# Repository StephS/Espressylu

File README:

This is a preliminary design for a 32bit control board, based on the Atmel SAM3A Microcontroller.
A few features:
4 Layer construction
Designed for 24v Operation
Native MicroSD
Polulu style stepper motor controllers

This board is designed for 24v operation only. A 20v OVLO is enabled on the main voltage regulator to prevent 12v operation. Because of this I removed any 12v power supply connectors.
The Hotbed, Hotend, Fan and Z Probe all have 24v connections. The Z Endstop uses a 4 pin configuration instead of a 3 pin. The extra pin supplies 24v for use with additional probes. Please be sure your probe can use 24v, or use an adapter with a 12v regulator to supply the normal 12v for the probe.

Since this version (version 0.6) is preliminary, I do not recommend its use until the design can be verified.
A BOM and PIN Mapping will be developed and shared as the design matures.

If you'd like to donate so I can buy the full version of Eagle, and make more cool stuff, please contact me through Google+ at https://plus.google.com/+StephanieS3D

Disclaimer:
These designs are provided without any warrenty, expressed or implied. This is a prototype designed for hobbiest use only.
Care should be taken during use and appropriate safety precautions taken.
The author is providing this item "as is". The author does not provide any warranty of the item whatsoever, whether express, implied, or statutory, including, but not limited to, any warranty of merchantability or fitness for a particular purpose or any warranty that the contents of the item will be error-free.
In no respect shall the author incur any liability for any damages, including, but limited to, direct, indirect, special, or consequential damages arising out of, resulting from, or any way connected to the use of the item, whether or not based upon warranty, contract, tort, or otherwise; whether or not injury was sustained by persons or property or otherwise; and whether or not loss was sustained from, or arose out of, the results of, the item, or any services that may be provided by the author.

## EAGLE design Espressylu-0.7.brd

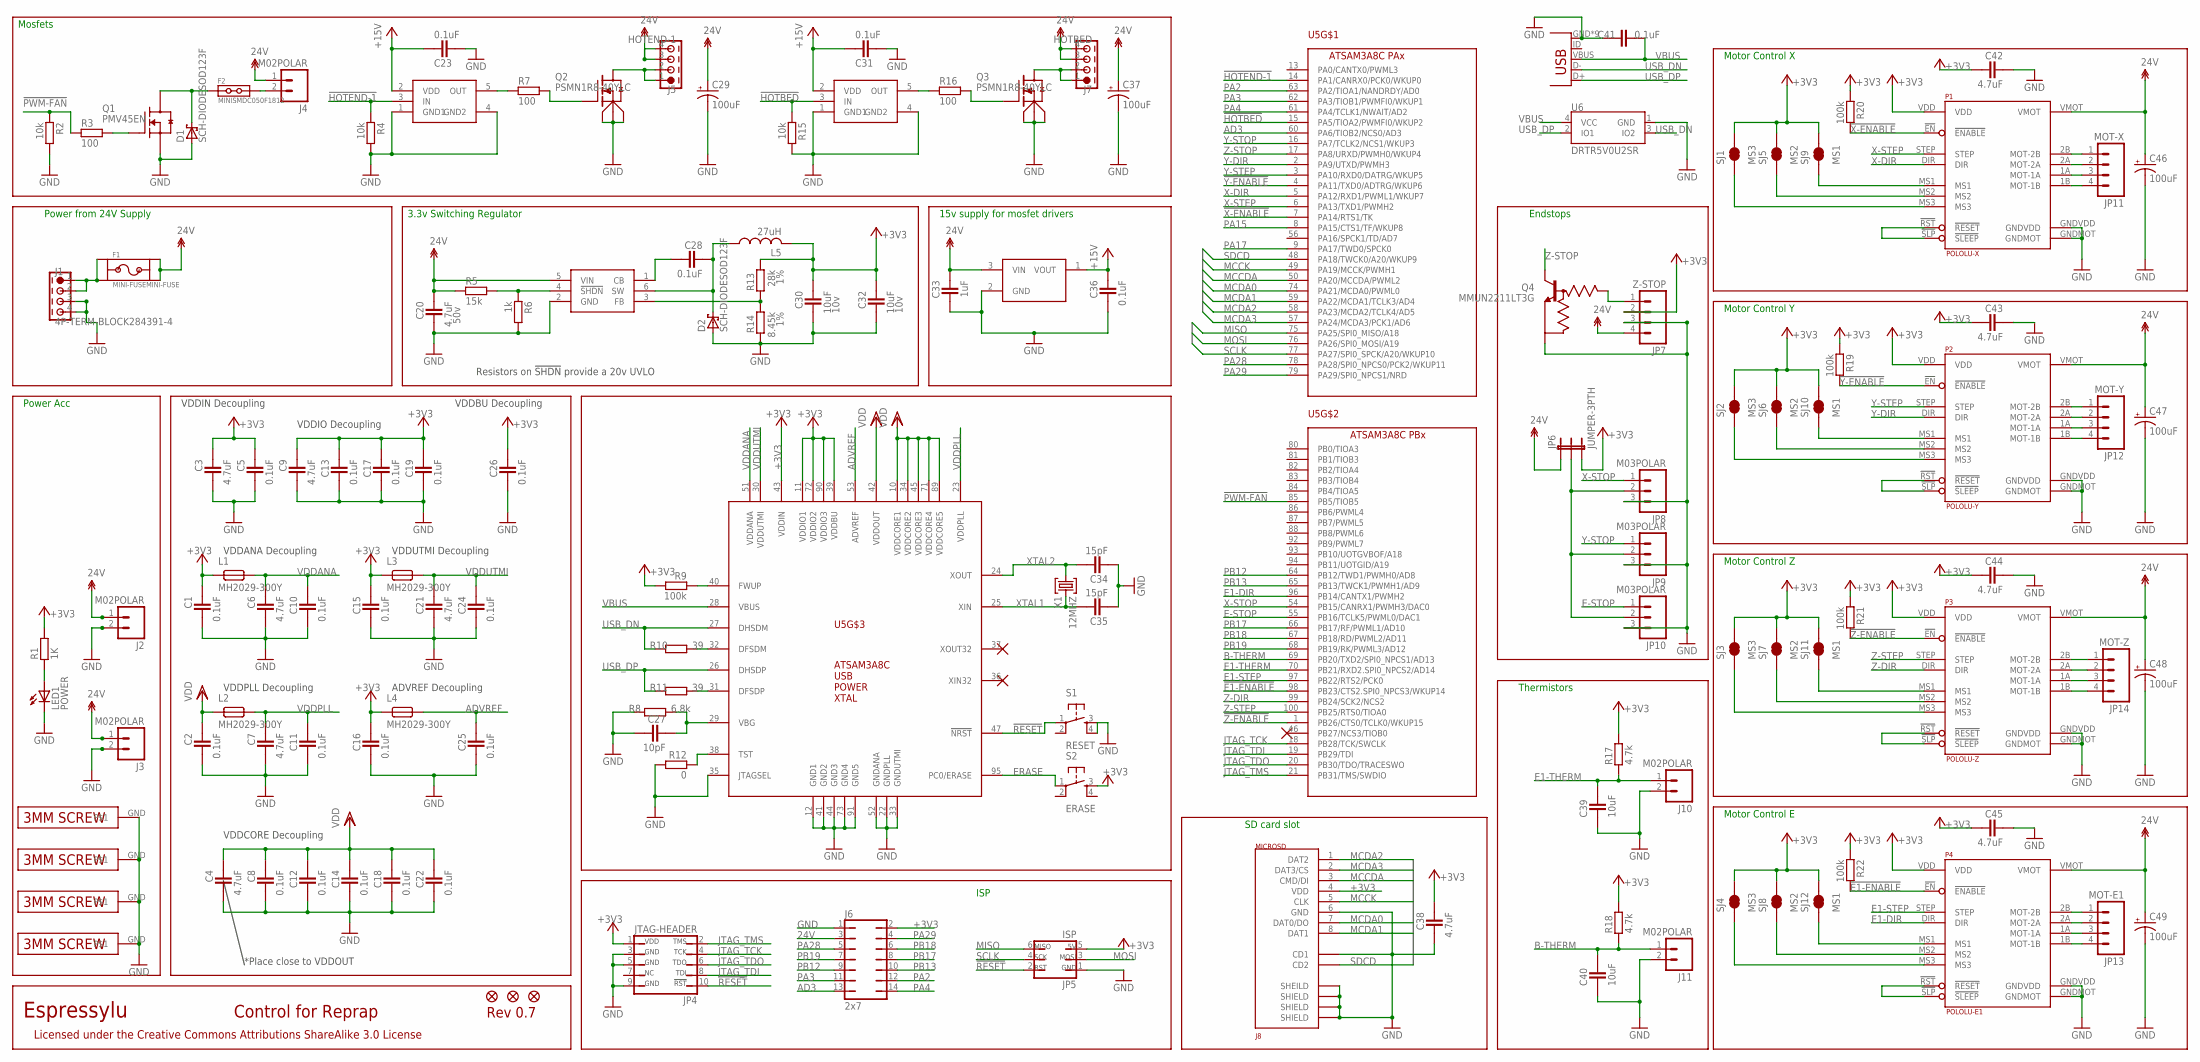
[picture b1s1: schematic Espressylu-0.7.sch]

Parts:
C1, C2, C5, C8, C10, C11, C12, C13, C14, C15, C16, C17, C18, C19, C22, C24, C25, C26: 0.1uF; CAPC1005X60N; TOLERANCE 10%; MANUFACTURER_PART_NUMBER CL05A104KQ5NNNC
C3, C4, C6, C7, C9, C21, C38, C42, C43, C44, C45: 4.7uF; CAPC1608X92N; TOLERANCE 10%; MANUFACTURER_PART_NUMBER CL10B475KQ8NQNC
C20: 4.7uF; CAPC3215X168N; TOLERANCE 10%; MANUFACTURER_PART_NUMBER UMK316AB7475KL-T
C23, C31, C36: 0.1uF; CAPC1005X60N; TOLERANCE 20%
C27: 10pF; CAPC1005X60N; TOLERANCE 5%; MANUFACTURER_PART_NUMBER CL10C100JB8NCNC
C28: 0.1uF; CAPC1005X60N; TOLERANCE 10%; MANUFACTURER_PART_NUMBER CL10B104KB8NNNC
C29, C37, C46, C47, C48, C49: 100uF; PANASONIC_D; TOLERANCE 20%; MANUFACTURER_PART_NUMBER EEE-FTH101XAP
C30, C32: 10uF; CAPC2012X145AN; TOLERANCE 10%; MANUFACTURER_PART_NUMBER GRM21BR71A106KE51L
C33: 1uF; CAPC1005X60N; TOLERANCE 20%
C34, C35: 15pF; CAPC1005X60N; TOLERANCE 5%; MANUFACTURER_PART_NUMBER CL05C150JB5NNNC
C39, C40: 10uF; CAPC1005X60N; TOLERANCE 20%; MANUFACTURER_PART_NUMBER GRM188R61C106MA73D
C41: 0.1uF; CAPC1005X60N; TOLERANCE 10%; MANUFACTURER_PART_NUMBER GRM188R71C104KA01D
D1: SCH-DIODESOD123F; SOD123F
D2: SCH-DIODESOD123F; SOD123F; MANUFACTURER_PART_NUMBER PMEG4010CEH,115
F1: MINI-FUSEMINI-FUSE; MINI_FUSE
F2: MINISMDC050F1812; MINISMDC
J1: 4P-TERM-BLOCK284391-4; 284391-4
J2, J3, J4, J10, J11: M02POLAR; MOLEX-1X2; MANUFACTURER_PART_NUMBER 0022272021
J5: HOTEND-1; 284391-4
J6: 2x7; JP7Q; MANUFACTURER_PART_NUMBER M20-9980746
J7: HOTBED; 284391-4
J8: MICROSD; AMPHENOL-MICROSD
J9: USB-MICRO-PTH; USB-MICROB-PTH
JP1, JP2, JP3: FIDUCIAL1X2.5; FIDUCIAL-1X2.5
JP4: JTAG-HEADER; 2X05-0.5-SMD
JP5: ISP
JP6: JUMPER-3PTH; 1X03
JP7: Z-STOP; MOLEX-1X4
JP8, JP9, JP10: M03POLAR; MOLEX-1X3; MANUFACTURER_PART_NUMBER 0022272031
JP11: MOT-X; MOLEX-1X4
JP12: MOT-Y; MOLEX-1X4
JP13: MOT-E1; MOLEX-1X4
JP14: MOT-Z; MOLEX-1X4
L1, L2, L3, L4: MH2029-300Y; FERRITE_BEAD_0805; MANUFACTURER_PART_NUMBER MH2029-300Y
L5: 27uH; SDR0604; MANUFACTURER_PART_NUMBER SDR0604-270YL
LED1: POWER; CHIPLED_0805; MANUFACTURER_PART_NUMBER APT2012SGC
P1: POLOLU-X; POLOLU-STEPPER-PTH
P2: POLOLU-Y; POLOLU-STEPPER-PTH
P3: POLOLU-Z; POLOLU-STEPPER-PTH
P4: POLOLU-E1; POLOLU-STEPPER-PTH
Q1: PMV45EN; SOT23C; VOLTAGE 60V; MANUFACTURER_PART_NUMBER IRLML2060TRPBF
Q2, Q3: PSMN1R8-40YLC; LFPACK-POWERPAK-SO8
Q4: MMUN2211LT3G; SOT23C; MANUFACTURER_PART_NUMBER MMUN2211LT3G
R1: 1K; RESC1608X55N
R2, R4, R15: 10k; RESC1005X40AN
R3, R7, R16: 100; RESC1005X40AN
R5: 15k; RESC1005X40AN
R6: 1k; RESC1005X40AN
R8: 6.8k; RESC1005X40AN; TOLERANCE 1%
R9, R19, R20, R21, R22: 100k; RESC1005X40AN
R10, R11: 39; RESC1005X40AN; TOLERANCE 1%
R12: 0; RESC1005X40AN
R13: 28k; RESC1005X40AN; TOLERANCE 1%
R14: 8.45k; RESC1005X40AN; TOLERANCE 1%
R17, R18: 4.7k; RESC1005X40AN
S1: RESET; SWITCH-SMD-4P
S2: ERASE; SWITCH-SMD-4P
SCREW1, SCREW2, SCREW3, SCREW4: 3MM-SCREW; PLATEDSCREW
SJ1, SJ2, SJ3, SJ4: MS3; SJ_2S-TRACE
SJ5, SJ6, SJ7, SJ8: MS2; SJ_2S-TRACE
SJ9, SJ10, SJ11, SJ12: MS1; SJ_2S-TRACE
U1, U3: MCP1402T; SOT23-5
U2: LMR16006X; TSOT6
U4: L78L15ABUTR; SOT89
U5: ATSAM3A8C-LQFP100; LQFP100
U6: DRTR5V0U2SR; SOT143-R
X1: 12MHZ; NDK-XTAL; MANUFACTURER_PART_NUMBER ABM3-12.000MHZ-B2-T

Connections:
5VREG_CB: C28.2, U2.1 (CB)
5VREG_FB: R13.2, R14.1, U2.3 (FB)
5VREG_SW: C28.1, D2.C, L5.1, U2.6 (SW)
12V_FUSE: F1.P$1, F1.P$2, J1.1, J1.2
24V: C20.1, C29.+, C33.1, C37.+, C46.+, C47.+, C48.+, C49.+, F1.P$3, F1.P$4, J2.1, J3.1, J4.1, J5.3, J5.4, J6.3, J7.3, J7.4, JP6.1, JP7.4, P1.VMOT, P2.VMOT, P3.VMOT, P4.VMOT, R5.1, U2.5 (VIN), U4.3 (VIN)
!E1-ENABLE: P4.!EN (!ENABLE), R22.2, U5.98 (PB23/CTS2.SPI0_NPCS3/WKUP14)
!HOTBED: R15.1, U3.3 (IN), U5.15 (PA5/TIOA2/PWMFI0/WKUP2)
!HOTEND-1: R4.1, U1.3 (IN), U5.14 (PA1/CANRX0/PCK0/WKUP0)
!PWM-FAN: R2.1, R3.1, U5.85 (PB5/TIOB5)
!RESET: JP4.10, JP5.2, S1.1, U5.47 (!NRST)
!X-ENABLE: P1.!EN (!ENABLE), R20.2, U5.7 (PA14/RTS1/TK)
!Y-ENABLE: P2.!EN (!ENABLE), R19.2, U5.4 (PA11/TXD0/ADTRG/WKUP6)
!Z-ENABLE: P3.!EN (!ENABLE), R21.2, U5.1 (PB26/CTS0/TCLK0/WKUP15)
+3V3: C1.1, C3.1, C5.1, C9.1, C13.1, C15.1, C16.1, C17.1, C19.1, C26.1, C30.1, C32.1, C38.1, C42.2, C43.2, C44.2, C45.2, J6.2, J8.4 (VDD), JP4.1, JP5.5, JP6.3, JP7.2, L1.1, L3.1, L4.1, L5.2, P1.VDD, P2.VDD, P3.VDD, P4.VDD, R1.2, R9.2, R13.1, R17.2, R18.2, R19.1, R20.1, R21.1, R22.1, S2.3, SJ1.2, SJ2.2, SJ3.2, SJ4.2, SJ5.2, SJ6.2, SJ7.2, SJ8.2, SJ9.2, SJ10.2, SJ11.2, SJ12.2, U5.11 (VDDIO1), U5.39 (VDDBU), U5.43 (VDDIN), U5.72 (VDDIO2), U5.90 (VDDIO3)
+15V: C23.1, C31.1, C36.1, U1.2 (VDD), U3.2 (VDD), U4.1 (VOUT)
AD3: J6.13, U5.60 (PA6/TIOB2/NCS0/AD3)
ADVREF: C25.1, L4.2, U5.53 (ADVREF)
B-THERM: C40.2, J11.1, R18.1, U5.69 (PB20/TXD2/SPI0_NPCS1/AD13)
E1-DIR: P4.DIR, U5.96 (PB14/CANTX1/PWMH2)
E1-STEP: P4.STEP, U5.97 (PB22/RTS2/PCK0)
E1-THERM: C39.2, J10.1, R17.1, U5.70 (PB21/RXD2.SPI0_NPCS2/AD14)
E-MOT-1A: JP13.3, P4.1A (MOT-1A)
E-MOT-1B: JP13.4, P4.1B (MOT-1B)
E-MOT-2A: JP13.2, P4.2A (MOT-2A)
E-MOT-2B: JP13.1, P4.2B (MOT-2B)
E-MS1: P4.MS1, SJ12.1
E-MS2: P4.MS2, SJ8.1
E-MS3: P4.MS3, SJ4.1
E-RESETSLEEP: P4.!RST (!RESET), P4.!SLP (!SLEEP)
E-STOP: JP10.1, U5.55 (PB16/TCLK5/PWML0/DAC1)
ENDSTOP+V: JP6.2, JP8.2, JP9.2, JP10.2
ERASE: S2.1, U5.95 (PC0/ERASE)
GND: C1.2, C2.2, C3.2, C4.2, C5.2, C6.2, C7.2, C8.2, C9.2, C10.2, C11.2, C12.2, C13.2, C14.2, C15.2, C16.2, C17.2, C18.2, C19.2, C20.2, C21.2, C22.2, C23.2, C24.2, C25.2, C26.2, C27.2, C29.-, C30.2, C31.2, C32.2, C33.2, C34.1, C35.1, C36.2, C37.-, C38.2, C39.1, C40.1, C41.1, C42.1, C43.1, C44.1, C45.1, C46.-, C47.-, C48.-, C49.-, D1.A, D2.A, J1.3, J1.4, J2.2, J3.2, J6.1, J8.6 (GND), J8.C1 (SHEILD), J8.C2 (SHIELD), J8.C3 (SHIELD), J8.C4 (SHIELD), J8.CD1, J9.GND, J9.GND1 (GND), J9.GND2 (GND), J9.GND3 (GND), J9.GND4 (GND), J9.GND5 (GND), J9.GND6 (GND), J9.GND7 (GND), J9.GND8 (GND), J10.2, J11.2, JP4.3, JP4.5, JP4.9, JP5.1, JP7.3, JP8.3, JP9.3, JP10.3, LED1.C, P1.GNDMOT, P1.GNDVDD, P2.GNDMOT, P2.GNDVDD, P3.GNDMOT, P3.GNDVDD, P4.GNDMOT, P4.GNDVDD, Q1.2 (S), Q2.1 (S1), Q2.2 (S2), Q2.3 (S3), Q3.1 (S1), Q3.2 (S2), Q3.3 (S3), Q4.2 (E), R2.2, R4.2, R6.2, R8.1, R12.2, R14.2, R15.2, S1.3, S1.4, SCREW1.GND, SCREW2.GND, SCREW3.GND, SCREW4.GND, U1.1 (GND1), U1.4 (GND2), U2.2 (GND), U3.1 (GND1), U3.4 (GND2), U4.2 (GND), U5.12 (GND1), U5.22 (GNDPLL), U5.33 (GNDUTMI), U5.35 (JTAGSEL), U5.41 (GND2), U5.44 (GND3), U5.52 (GNDANA), U5.73 (GND4), U5.91 (GND5), U6.1 (GND)
HOTBED-GND: J7.1, J7.2, Q3.5-8 (D)
HOTEND-GND: J5.1, J5.2, Q2.5-8 (D)
JTAG_TCK: JP4.4, U5.18 (PB28/TCK/SWCLK)
JTAG_TDI: JP4.8, U5.19 (PB29/TDI)
JTAG_TDO: JP4.6, U5.20 (PB30/TDO/TRACESWO)
JTAG_TMS: JP4.2, U5.21 (PB31/TMS/SWDIO)
MCCDA: J8.3 (CMD/DI), U5.50 (PA20/MCCDA/PWML2)
MCCK: J8.5 (CLK), U5.49 (PA19/MCCK/PWMH1)
MCDA0: J8.7 (DAT0/DO), U5.74 (PA21/MCDA0/PWML0)
MCDA1: J8.8 (DAT1), U5.59 (PA22/MCDA1/TCLK3/AD4)
MCDA2: J8.1 (DAT2), U5.58 (PA23/MCDA2/TCLK4/AD5)
MCDA3: J8.2 (DAT3/CS), U5.57 (PA24/MCDA3/PCK1/AD6)
MISO: JP5.6, U5.75 (PA25/SPI0_MISO/A18)
MOSI: JP5.3, U5.76 (PA26/SPI0_MOSI/A19)
unnamed: LED1.A, R1.1
unnamed: Q3.4 (G), R16.2
unnamed: R5.2, R6.1, U2.4 (!SHDN)
unnamed: R9.1, U5.40 (FWUP)
unnamed: F2.P$2, J4.2
unnamed: D1.C, F2.P$1, Q1.3 (D)
unnamed: R12.1, U5.38 (TST)
unnamed: R10.2, U5.32 (DFSDM)
unnamed: Q1.1 (G), R3.2
unnamed: Q2.4 (G), R7.2
unnamed: R11.2, U5.31 (DFSDP)
unnamed: R16.1, U3.5 (OUT)
unnamed: R7.1, U1.5 (OUT)
PA2: J6.12, U5.63 (PA2/TIOA1/NANDRDY/AD0)
PA3: J6.11, U5.62 (PA3/TIOB1/PWMFI0/WKUP1)
PA4: J6.14, U5.61 (PA4/TCLK1/NWAIT/AD2)
PA15: U5.8 (PA15/CTS1/TF/WKUP8)
PA17: U5.9 (PA17/TWD0/SPCK0)
PA28: J6.5, U5.78 (PA28/SPI0_NPCS0/PCK2/WKUP11)
PA29: J6.4, U5.79 (PA29/SPI0_NPCS1/NRD)
PB12: J6.9, U5.64 (PB12/TWD1/PWMH0/AD8)
PB13: J6.10, U5.65 (PB13/TWCK1/PWMH1/AD9)
PB17: J6.8, U5.66 (PB17/RF/PWML1/AD10)
PB18: J6.6, U5.67 (PB18/RD/PWML2/AD11)
PB19: J6.7, U5.68 (PB19/RK/PWML3/AD12)
SCLK: JP5.4, U5.77 (PA27/SPI0_SPCK/A20/WKUP10)
SDCD: J8.CD2, U5.48 (PA18/TWCK0/A20/WKUP9)
USB_DN: J9.D-, R10.1, U5.27 (DHSDM), U6.3 (IO2)
USB_DP: J9.D+, R11.1, U5.26 (DHSDP), U6.2 (IO1)
VBG: C27.1, R8.2, U5.29 (VBG)
VBUS: C41.2, J9.VBUS, U5.28 (VBUS), U6.4 (VCC)
VDD: C2.1, C4.1, C8.1, C12.1, C14.1, C18.1, C22.1, L2.1, U5.10 (VDDCORE1), U5.34 (VDDCORE2), U5.42 (VDDOUT), U5.45 (VDDCORE3), U5.71 (VDDCORE4), U5.89 (VDDCORE5)
VDDANA: C6.1, C10.1, L1.2, U5.51 (VDDANA)
VDDPLL: C7.1, C11.1, L2.2, U5.23 (VDDPLL)
VDDUTMI: C21.1, C24.1, L3.2, U5.30 (VDDUTMI)
X-DIR: P1.DIR, U5.5 (PA12/RXD1/PWML1/WKUP7)
X-MOT-1A: JP11.3, P1.1A (MOT-1A)
X-MOT-1B: JP11.4, P1.1B (MOT-1B)
X-MOT-2A: JP11.2, P1.2A (MOT-2A)
X-MOT-2B: JP11.1, P1.2B (MOT-2B)
X-MS1: P1.MS1, SJ9.1
X-MS2: P1.MS2, SJ5.1
X-MS3: P1.MS3, SJ1.1
X-RESETSLEEP: P1.!RST (!RESET), P1.!SLP (!SLEEP)
X-STEP: P1.STEP, U5.6 (PA13/TXD1/PWMH2)
X-STOP: JP8.1, U5.54 (PB15/CANRX1/PWMH3/DAC0)
XTAL1: C35.2, U5.25 (XIN), X1.P$2 (2)
XTAL2: C34.2, U5.24 (XOUT), X1.P$1 (1)
Y-DIR: P2.DIR, U5.2 (PA9/UTXD/PWMH3)
Y-MOT-1A: JP12.3, P2.1A (MOT-1A)
Y-MOT-1B: JP12.4, P2.1B (MOT-1B)
Y-MOT-2A: JP12.2, P2.2A (MOT-2A)
Y-MOT-2B: JP12.1, P2.2B (MOT-2B)
Y-MS1: P2.MS1, SJ10.1
Y-MS2: P2.MS2, SJ6.1
Y-MS3: P2.MS3, SJ2.1
Y-RESETSLEEP: P2.!RST (!RESET), P2.!SLP (!SLEEP)
Y-STEP: P2.STEP, U5.3 (PA10/RXD0/DATRG/WKUP5)
Y-STOP: JP9.1, U5.16 (PA7/TCLK2/NCS1/WKUP3)
Z-DIR: P3.DIR, U5.99 (PB24/SCK2/NCS2)
Z-MOT-1A: JP14.3, P3.1A (MOT-1A)
Z-MOT-1B: JP14.4, P3.1B (MOT-1B)
Z-MOT-2A: JP14.2, P3.2A (MOT-2A)
Z-MOT-2B: JP14.1, P3.2B (MOT-2B)
Z-MS1: P3.MS1, SJ11.1
Z-MS2: P3.MS2, SJ7.1
Z-MS3: P3.MS3, SJ3.1
Z-RESETSLEEP: P3.!RST (!RESET), P3.!SLP (!SLEEP)
Z-STEP: P3.STEP, U5.100 (PB25/RTS0/TIOA0)
Z-STOP: Q4.3 (C), U5.17 (PA8/URXD/PWMH0/WKUP4)
Z-STOP-BIAS: JP7.1, Q4.1 (B)

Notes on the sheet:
Motor Control X
Motor Control Y
Motor Control Z
Motor Control E
ISP
Thermistors
Endstops
Mosfets
Power Acc
Espressylu
Rev 0.7
Control for Reprap
Licensed under the Creative Commons Attributions ShareAlike 3.0 License
15v supply for mosfet drivers
Power from 24V Supply
3.3v Switching Regulator
SD card slot
VDDCORE Decoupling
VDDIN Decoupling
VDDPLL Decoupling
VDDIO Decoupling
VDDANA Decoupling
VDDUTMI Decoupling
*Place close to VDDOUT
VDDBU Decoupling
ADVREF Decoupling
Resistors on !SHDN! provide a 20v UVLO

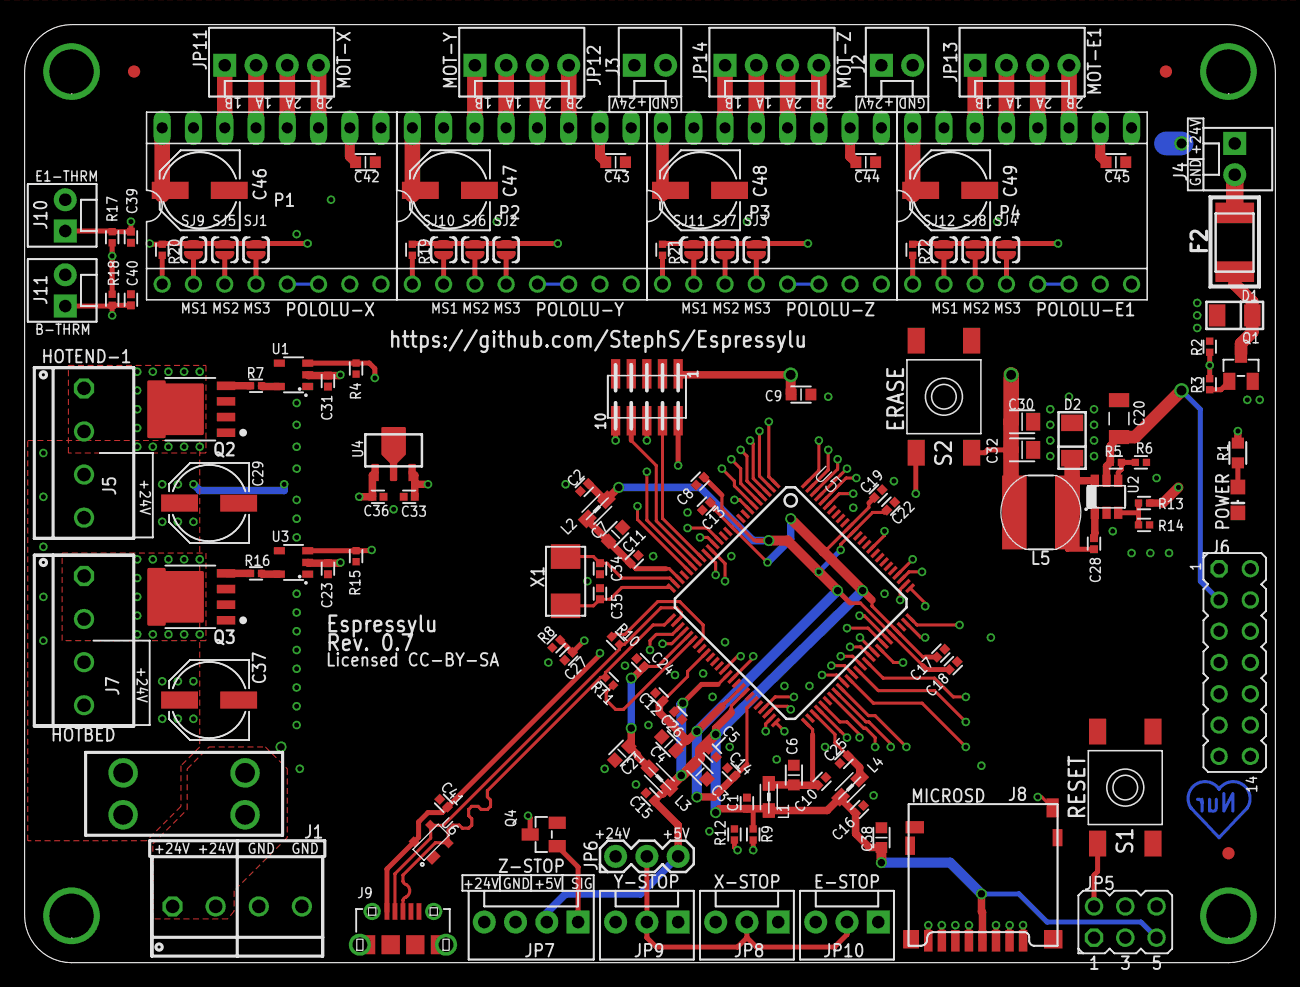
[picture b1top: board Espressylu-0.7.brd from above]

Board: 4 copper layers, 101.6 x 76.2 mm, 139 parts (0 on the bottom side), 116 nets.

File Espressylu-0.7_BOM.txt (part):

Part   Value                 Device                     Package             Description                          CURRENT DCR  DESCRIPTION                               ESR    IRMS MANUFACTURER            MANUFACTURER_PART_NUMBER NOTES                                                                       RDS_ON  REVERSE_VOLTAGE TOLERANCE VDC  VGS   VOLTAGE
C1     0.1uF                 CAPACITOR_0402             CAPC1005X60N                                                                                                                Samsung                 CL05A104KQ5NNNC                                                                                                              10%       6.3V              
C2     0.1uF                 CAPACITOR_0402             CAPC1005X60N                                                                                                                Samsung                 CL05A104KQ5NNNC                                                                                                              10%       6.3V              
C3     4.7uF                 CAPACITOR_0603             CAPC1608X92N                                                                                                                Samsung                 CL10B475KQ8NQNC                                                                                                              10%       6.3V              
C4     4.7uF                 CAPACITOR_0603             CAPC1608X92N                                                                                                                Samsung                 CL10B475KQ8NQNC                                                                                                              10%       6.3V              
C5     0.1uF                 CAPACITOR_0402             CAPC1005X60N                                                                                                                Samsung                 CL05A104KQ5NNNC                                                                                                              10%       6.3V              
C6     4.7uF                 CAPACITOR_0603             CAPC1608X92N                                                                                                                Samsung                 CL10B475KQ8NQNC                                                                                                              10%       6.3V              
C7     4.7uF                 CAPACITOR_0603             CAPC1608X92N                                                                                                                Samsung                 CL10B475KQ8NQNC                                                                                                              10%       6.3V              
C8     0.1uF                 CAPACITOR_0402             CAPC1005X60N                                                                                                                Samsung                 CL05A104KQ5NNNC                                                                                                              10%       6.3V              
C9     4.7uF                 CAPACITOR_0603             CAPC1608X92N                                                                                                                Samsung                 CL10B475KQ8NQNC                                                                                                              10%       6.3V              
C10    0.1uF                 CAPACITOR_0402             CAPC1005X60N                                                                                                                Samsung                 CL05A104KQ5NNNC                                                                                                              10%       6.3V              
C11    0.1uF                 CAPACITOR_0402             CAPC1005X60N                                                                                                                Samsung                 CL05A104KQ5NNNC                                                                                                              10%       6.3V              
C12    0.1uF                 CAPACITOR_0402             CAPC1005X60N                                                                                                                Samsung                 CL05A104KQ5NNNC                                                                                                              10%       6.3V              
C13    0.1uF                 CAPACITOR_0402             CAPC1005X60N                                                                                                                Samsung                 CL05A104KQ5NNNC                                                                                                              10%       6.3V              
C14    0.1uF                 CAPACITOR_0402             CAPC1005X60N                                                                                                                Samsung                 CL05A104KQ5NNNC                                                                                                              10%       6.3V              
C15    0.1uF                 CAPACITOR_0402             CAPC1005X60N                                                                                                                Samsung                 CL05A104KQ5NNNC                                                                                                              10%       6.3V              
C16    0.1uF                 CAPACITOR_0402             CAPC1005X60N                                                                                                                Samsung                 CL05A104KQ5NNNC                                                                                                              10%       6.3V              
C17    0.1uF                 CAPACITOR_0402             CAPC1005X60N                                                                                                                Samsung                 CL05A104KQ5NNNC                                                                                                              10%       6.3V              
C18    0.1uF                 CAPACITOR_0402             CAPC1005X60N                                                                                                                Samsung                 CL05A104KQ5NNNC                                                                                                              10%       6.3V              
C19    0.1uF                 CAPACITOR_0402             CAPC1005X60N                                                                                                                Samsung                 CL05A104KQ5NNNC                                                                                                              10%       6.3V              
C20    4.7uF                 CAPACITOR_1206             CAPC3215X168N                                                                                                               Yaiyo Yuden             UMK316AB7475KL-T                                                                                                             10%       50v               
C21    4.7uF                 CAPACITOR_0603             CAPC1608X92N                                                                                                                Samsung                 CL10B475KQ8NQNC                                                                                                              10%       6.3V              
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
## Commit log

2015-10-06 :lollipop: Added .gitattributes & .gitignore files
2015-10-06 First public revision 0.6
    Preliminary design, not recommended for manufacturing.
2015-10-06 Adding board layout picture
2015-10-07 Layout cleanup
    Moved the stepper motor headers closer to the connectors. Cleaned up the
    schematic and labels.
2015-12-01 Cleaned up Silkscreen and added caps
    I cleaned up the silkscreen for all of the components.
    Capacitors were added to the motor driver VCC pins.
    More GND Vias were added to reduce noise.
    The mosfets were shifted away from the connectors slightly.
    The stepper motor connectors were shifted slightly closer to the edge of
    the board.

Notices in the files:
Espressylu-0.7.brd:
Licensed CC-BY-SA
